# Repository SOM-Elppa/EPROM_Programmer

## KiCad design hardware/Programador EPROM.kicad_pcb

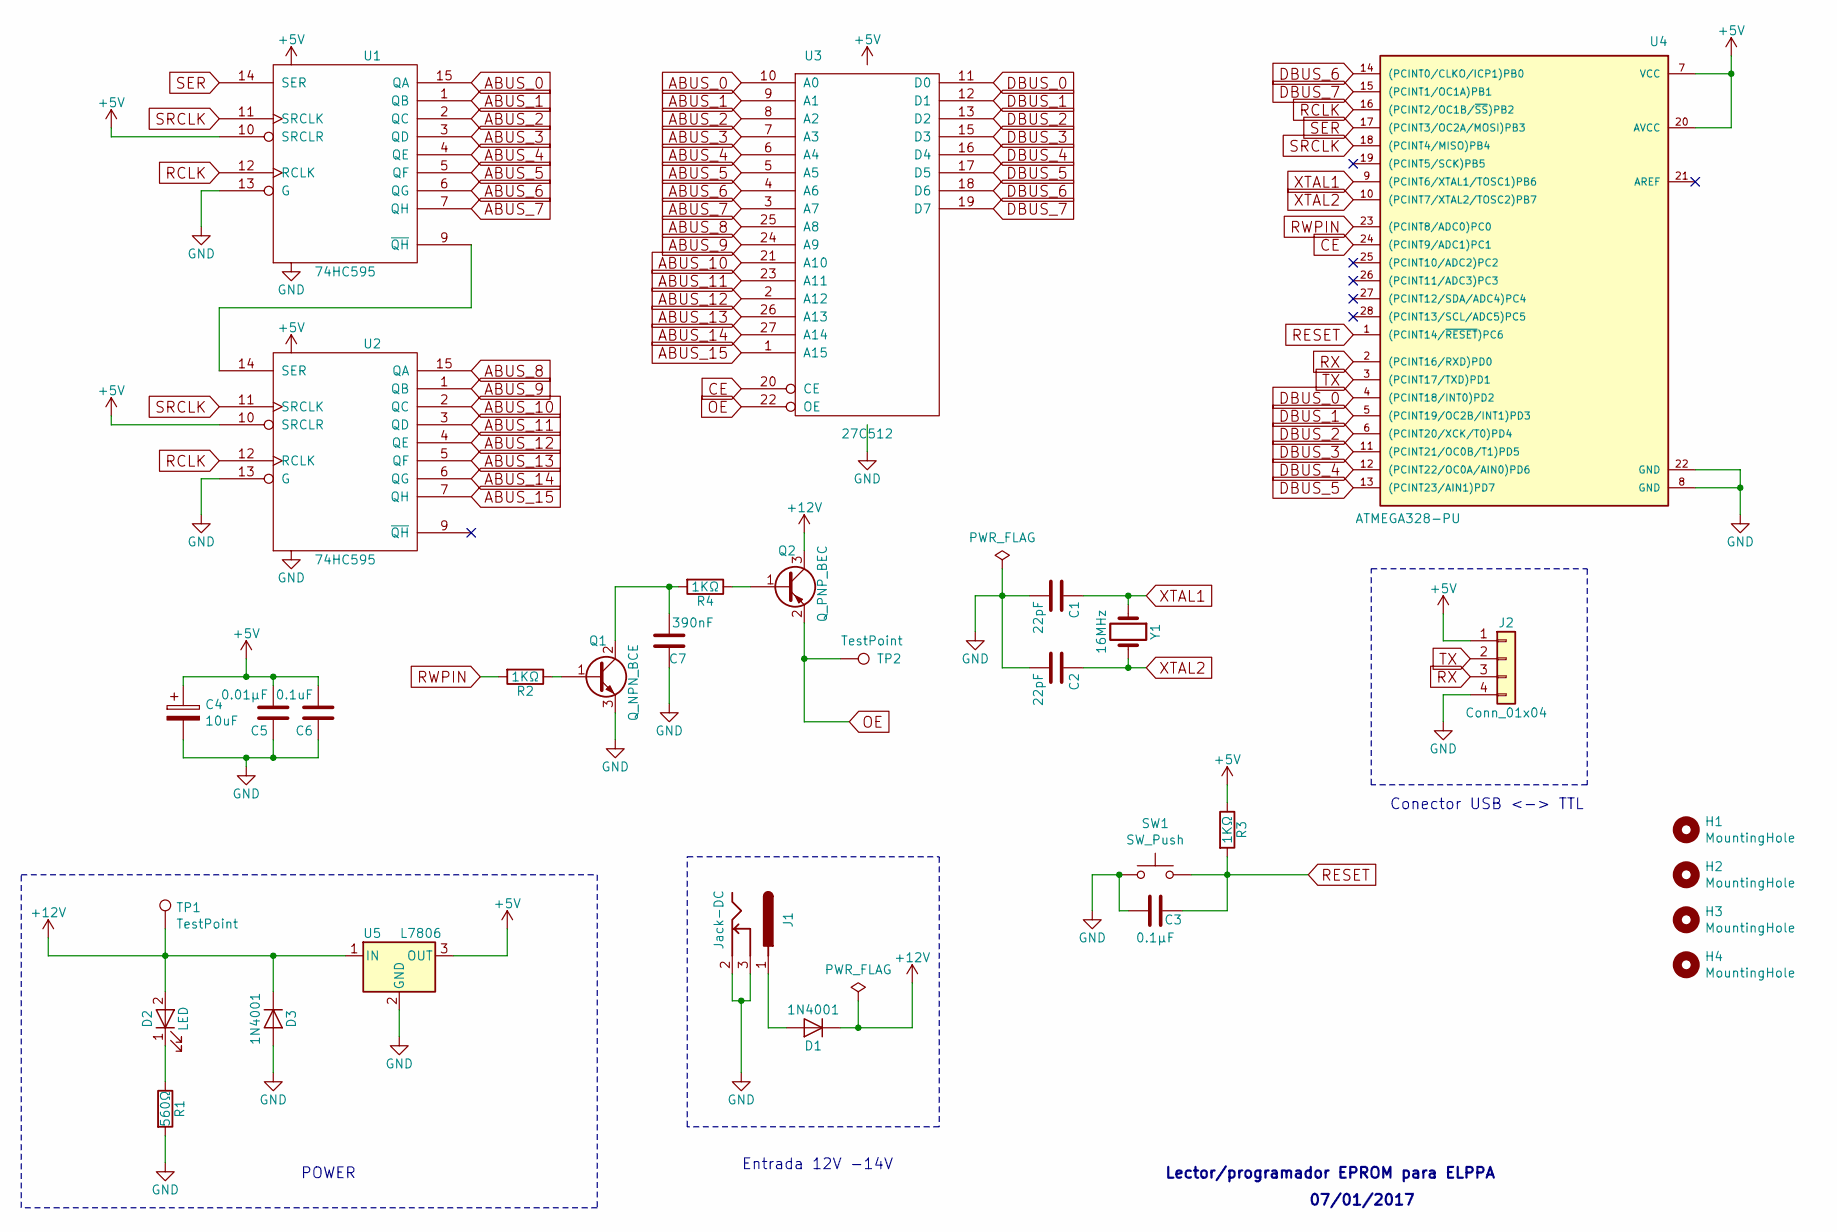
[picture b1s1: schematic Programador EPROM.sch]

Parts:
C1, C2: 22pF; C_Disc_D3.0mm_W1.6mm_P2.50mm
C3: 0.1µF; C_Disc_D3.0mm_W1.6mm_P2.50mm
C4: 10uF; CP_Radial_D5.0mm_P2.50mm
C5: 0.01µF; C_Disc_D3.0mm_W1.6mm_P2.50mm
C6: 0.1uF; C_Disc_D3.0mm_W1.6mm_P2.50mm
C7: 390nF; C_Disc_D3.0mm_W1.6mm_P2.50mm
D1: 1N4001; D_5W_P12.70mm_Horizontal
D2: LED; LED_D5.0mm
D3: 1N4001; D_A-405_P7.62mm_Horizontal
H1, H2, H3, H4: MountingHole; MountingHole_3.2mm_M3
J1: Jack-DC; BarrelJack_Horizontal
J2: Conn_01x04; PinHeader_1x04_P2.54mm_Vertical
Q1: Q_NPN_BCE; TO-92_Inline
Q2: Q_PNP_BEC; TO-92_Inline
R1: 560Ω; R_Axial_DIN0207_L6.3mm_D2.5mm_P10.16mm_Horizontal
R2, R3, R4: 1KΩ; R_Axial_DIN0207_L6.3mm_D2.5mm_P10.16mm_Horizontal
SW1: SW_Push; SW_PUSH_6mm_H5mm
TP1, TP2: TestPoint; TestPoint_Pad_2.5x2.5mm
U1, U2: 74HC595; DIP-16_W7.62mm
U3: 27C512; DIP-28_W15.24mm
U4: ATMEGA328-PU; DIP-28_W7.62mm_LongPads
U5: L7806; TO-220-3_Vertical
Y1: 16MHz; Crystal_HC49-4H_Vertical

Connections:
+5V: C4.1, C5.2, C6.2, J2.1, R3.1, U1.10 (SRCLR), U1.16 (VCC), U2.10 (SRCLR), U2.16 (VCC), U3.28 (VCC), U4.7 (VCC), U4.20 (AVCC), U5.3 (OUT)
+12V: D1.1 (K), D2.2 (A), D3.1 (K), Q2.3 (C), TP1.1, U5.1 (IN)
ABUS_0: U1.15 (QA), U3.10 (A0)
ABUS_1: U1.1 (QB), U3.9 (A1)
ABUS_2: U1.2 (QC), U3.8 (A2)
ABUS_3: U1.3 (QD), U3.7 (A3)
ABUS_4: U1.4 (QE), U3.6 (A4)
ABUS_5: U1.5 (QF), U3.5 (A5)
ABUS_6: U1.6 (QG), U3.4 (A6)
ABUS_7: U1.7 (QH), U3.3 (A7)
ABUS_8: U2.15 (QA), U3.25 (A8)
ABUS_9: U2.1 (QB), U3.24 (A9)
ABUS_10: U2.2 (QC), U3.21 (A10)
ABUS_11: U2.3 (QD), U3.23 (A11)
ABUS_12: U2.4 (QE), U3.2 (A12)
ABUS_13: U2.5 (QF), U3.26 (A13)
ABUS_14: U2.6 (QG), U3.27 (A14)
ABUS_15: U2.7 (QH), U3.1 (A15)
CE: U3.20 (CE), U4.24 ((PCINT9/ADC1)PC1)
DBUS_0: U3.11 (D0), U4.4 ((PCINT18/INT0)PD2)
DBUS_1: U3.12 (D1), U4.5 ((PCINT19/OC2B/INT1)PD3)
DBUS_2: U3.13 (D2), U4.6 ((PCINT20/XCK/T0)PD4)
DBUS_3: U3.15 (D3), U4.11 ((PCINT21/OC0B/T1)PD5)
DBUS_4: U3.16 (D4), U4.12 ((PCINT22/OC0A/AIN0)PD6)
DBUS_5: U3.17 (D5), U4.13 ((PCINT23/AIN1)PD7)
DBUS_6: U3.18 (D6), U4.14 ((PCINT0/CLKO/ICP1)PB0)
DBUS_7: U3.19 (D7), U4.15 ((PCINT1/OC1A)PB1)
GND: C1.2, C2.2, C3.2, C4.2, C5.1, C6.1, C7.1, D3.2 (A), J1.2, J1.3, J2.4, Q1.3 (E), R1.2, SW1.1, U1.8 (GND), U1.13 (G), U2.8 (GND), U2.13 (G), U3.14 (GND), U4.8 (GND), U4.22 (GND), U5.2 (GND)
unnamed: C7.2, Q1.2 (C), R4.2
unnamed: D1.2 (A), J1.1
unnamed: D2.1 (K), R1.1
unnamed: Q1.1 (B), R2.1
unnamed: Q2.1 (B), R4.1
unnamed: U1.9 (~QH), U2.14 (SER)
OE: Q2.2 (E), TP2.1, U3.22 (OE)
RCLK: U1.12 (RCLK), U2.12 (RCLK), U4.16 ((PCINT2/OC1B/~SS~)PB2)
RESET: C3.1, R3.2, SW1.2, U4.1 ((PCINT14/~RESET~)PC6)
RWPIN: R2.2, U4.23 ((PCINT8/ADC0)PC0)
RX: J2.3, U4.2 ((PCINT16/RXD)PD0)
SER: U1.14 (SER), U4.17 ((PCINT3/OC2A/MOSI)PB3)
SRCLK: U1.11 (SRCLK), U2.11 (SRCLK), U4.18 ((PCINT4/MISO)PB4)
TX: J2.2, U4.3 ((PCINT17/TXD)PD1)
XTAL1: C1.1, U4.9 ((PCINT6/XTAL1/TOSC1)PB6), Y1.1
XTAL2: C2.1, U4.10 ((PCINT7/XTAL2/TOSC2)PB7), Y1.2

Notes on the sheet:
Lector/programador EPROM para ELPPA
07/01/2017
Conector USB <-> TTL
Entrada 12V -14V
POWER

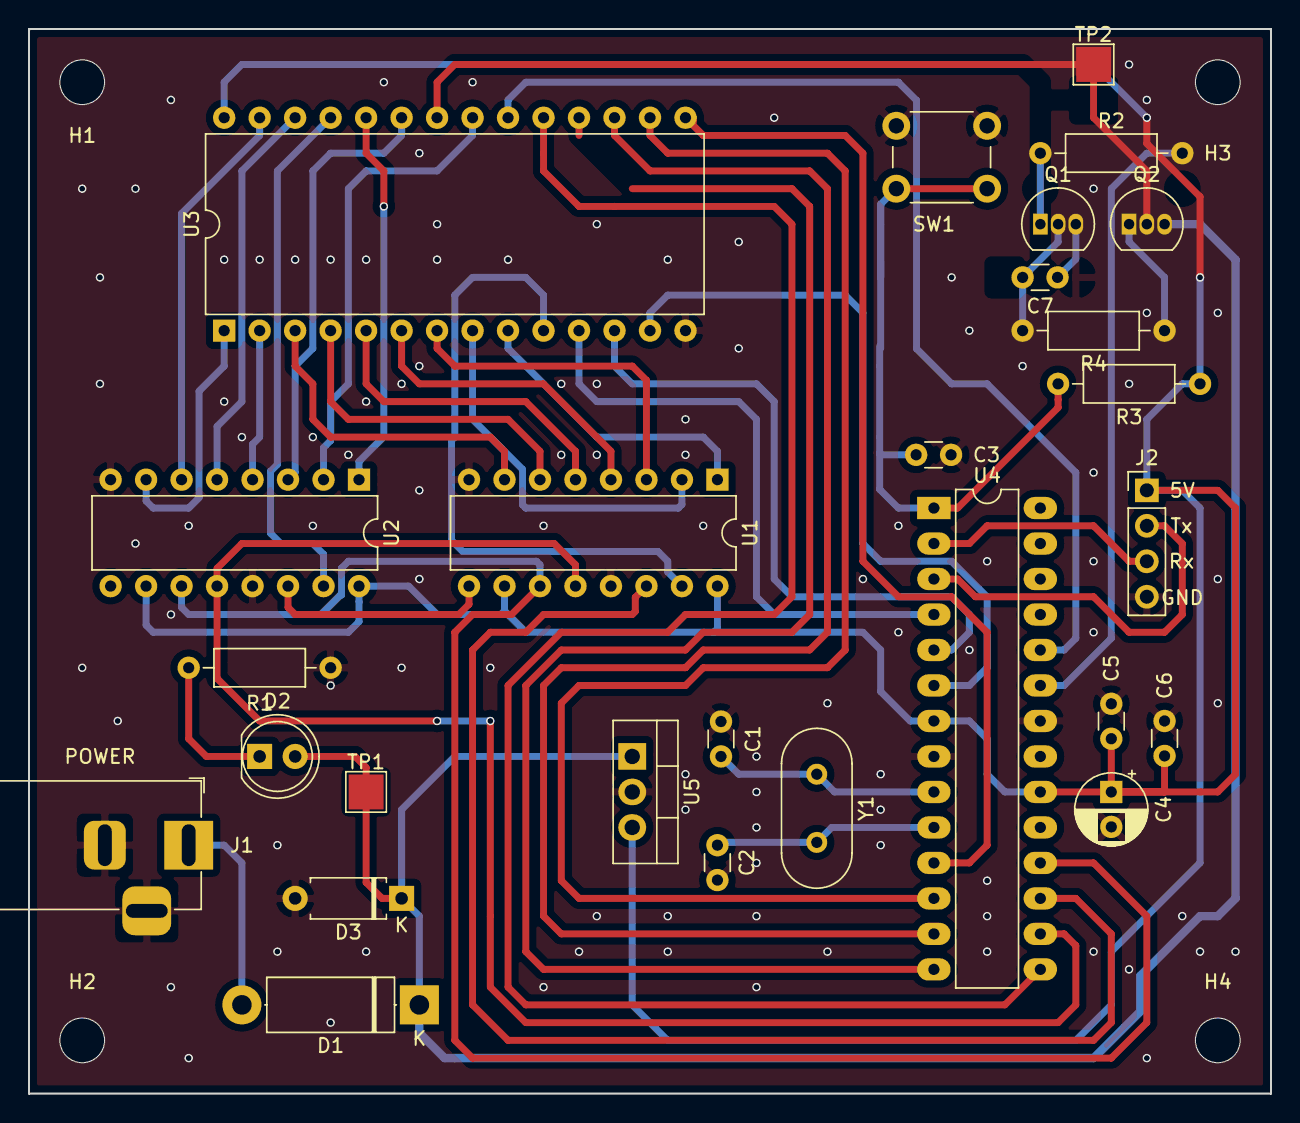
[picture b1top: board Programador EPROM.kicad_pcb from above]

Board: 2 copper layers, 88.9 x 76.2 mm, 31 parts (0 on the bottom side), 44 nets.

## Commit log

2020-11-06 modified .gitignore
2020-11-06 added Arduino firmware
2020-11-06 added programmer KiCAD files
2020-11-06 added EEPROM programmer PC GUI
